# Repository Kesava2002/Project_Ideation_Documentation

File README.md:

# Project Ideation 
## Documentation
Documentation of ideation done by previous project members for "Digital Pen"

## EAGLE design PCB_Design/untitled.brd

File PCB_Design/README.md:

# PCB Design with Eagle
Project Task 1 was meant to introduce us into the world of PCB design. 
## Video 1:
Introduction in Schematics    
1. Creating schematics file in Eagle
2. Adding Libraries  
3. Adding, deleting, moving components of the circuit  
4. Completing the circuit by joining different components

## Video 2:
Converting schematics into Circuit boards  
1. Creating a .brd file for the .sch file
2. Adding the components onto the circuit board area and using RATSNEST to optimise connections
3. Grounding the Top and Bottom layers for the purpose of cooling and acting as a ground for connections  
4. Manual/Auto routing of connections to form the circuit board 

## Video 3:
Circuit Manufacturing  
Exporting the circuit into gerber files for manufacturing

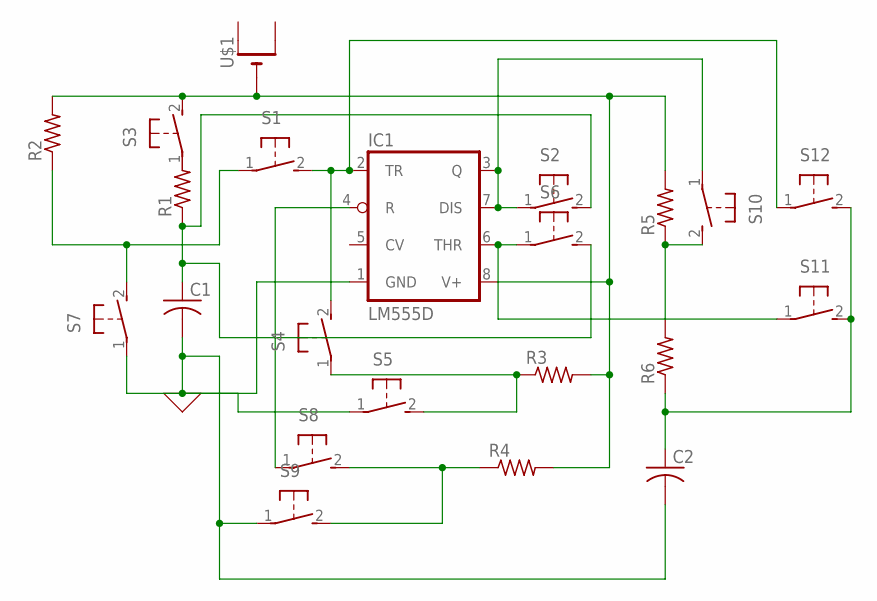
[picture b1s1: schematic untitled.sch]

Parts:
C1, C2: C-US025-025X050; C025-025X050
IC1: LM555D; SO08
R1, R2, R3, R4, R5, R6: R-US_0411/15; 0411/15
S1, S2, S3, S4, S5, S6, S7, S8, S9, S10, S11, S12: 31-XX; B3F-31XX
U$1: CR1220SMT; CR1220-SMD

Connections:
unnamed: C1.1, R1.1, S2.2 (S), S6.2 (S)
unnamed: C1.2, C2.2, IC1.1 (GND), S5.1, S7.1, S9.1
unnamed: IC1.3 (Q), IC1.7 (DIS), S2.1, S10.1
unnamed: IC1.2 (TR), S1.2 (S), S4.2 (S), S12.1
unnamed: IC1.6 (THR), S6.1, S11.1
unnamed: R3.1, S4.1, S5.2 (S)
unnamed: R2.1, S1.1, S7.2 (S)
unnamed: IC1.4 (R), S8.1
unnamed: R4.1, S8.2 (S), S9.2 (S)
unnamed: IC1.8 (V+), R2.2, R3.2, R4.2, R5.2, S3.2 (S), U$1.-
unnamed: R5.1, R6.2, S10.2 (S)
unnamed: C2.1, R6.1, S11.2 (S), S12.2 (S)

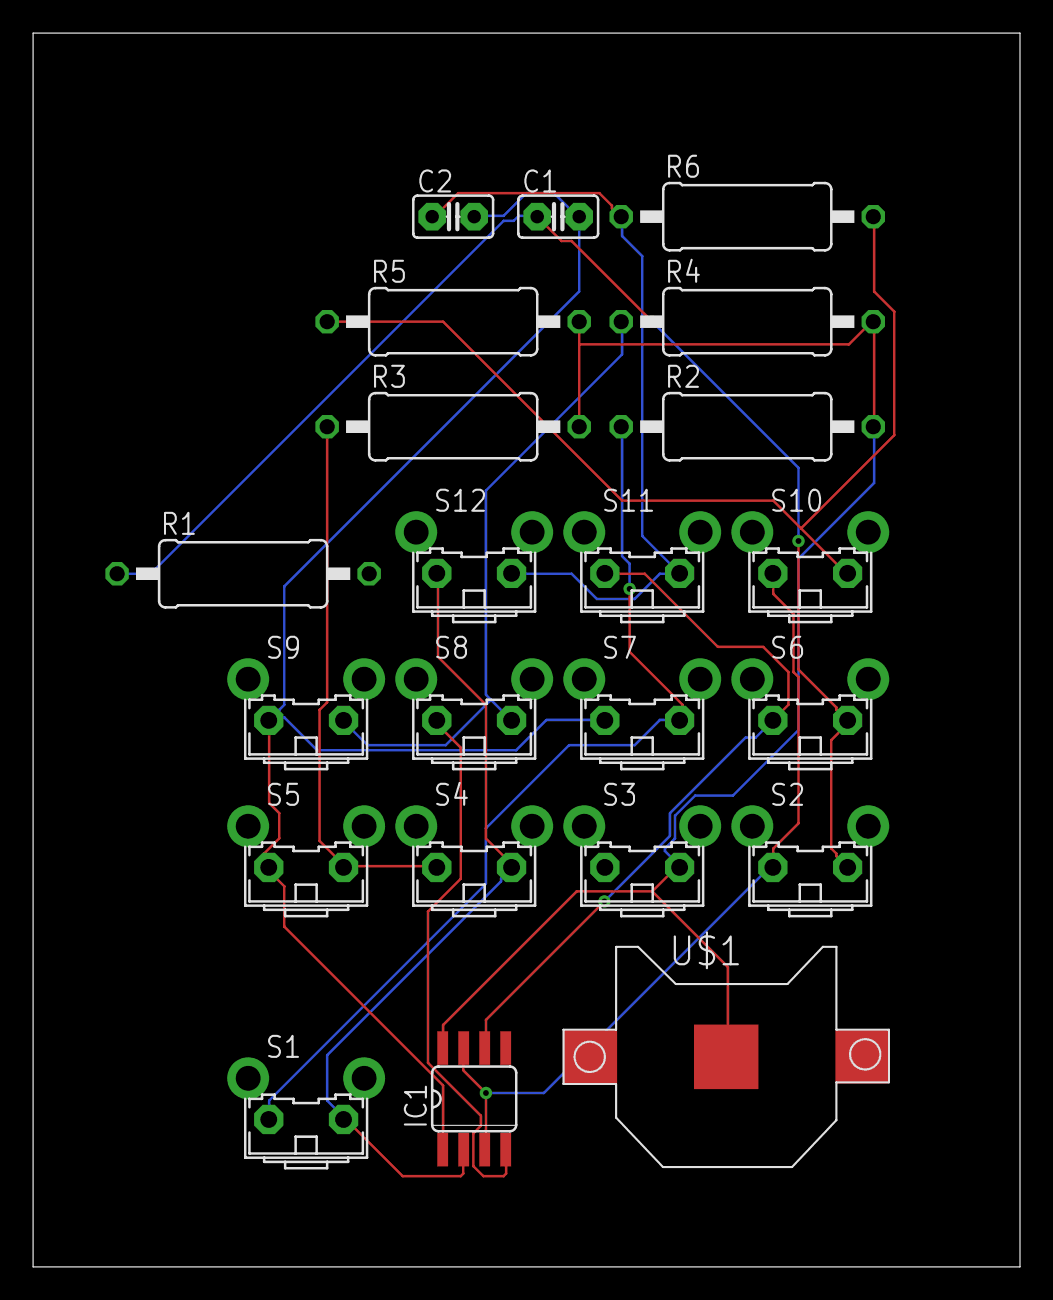
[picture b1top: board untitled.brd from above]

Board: 2 copper layers, 59.7 x 74.6 mm, 22 parts (0 on the bottom side), 12 nets.

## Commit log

2021-06-13 Rename untitled.brd to 555timer.brd
2021-06-13 Rename untitled.sch to 555timer.sch
